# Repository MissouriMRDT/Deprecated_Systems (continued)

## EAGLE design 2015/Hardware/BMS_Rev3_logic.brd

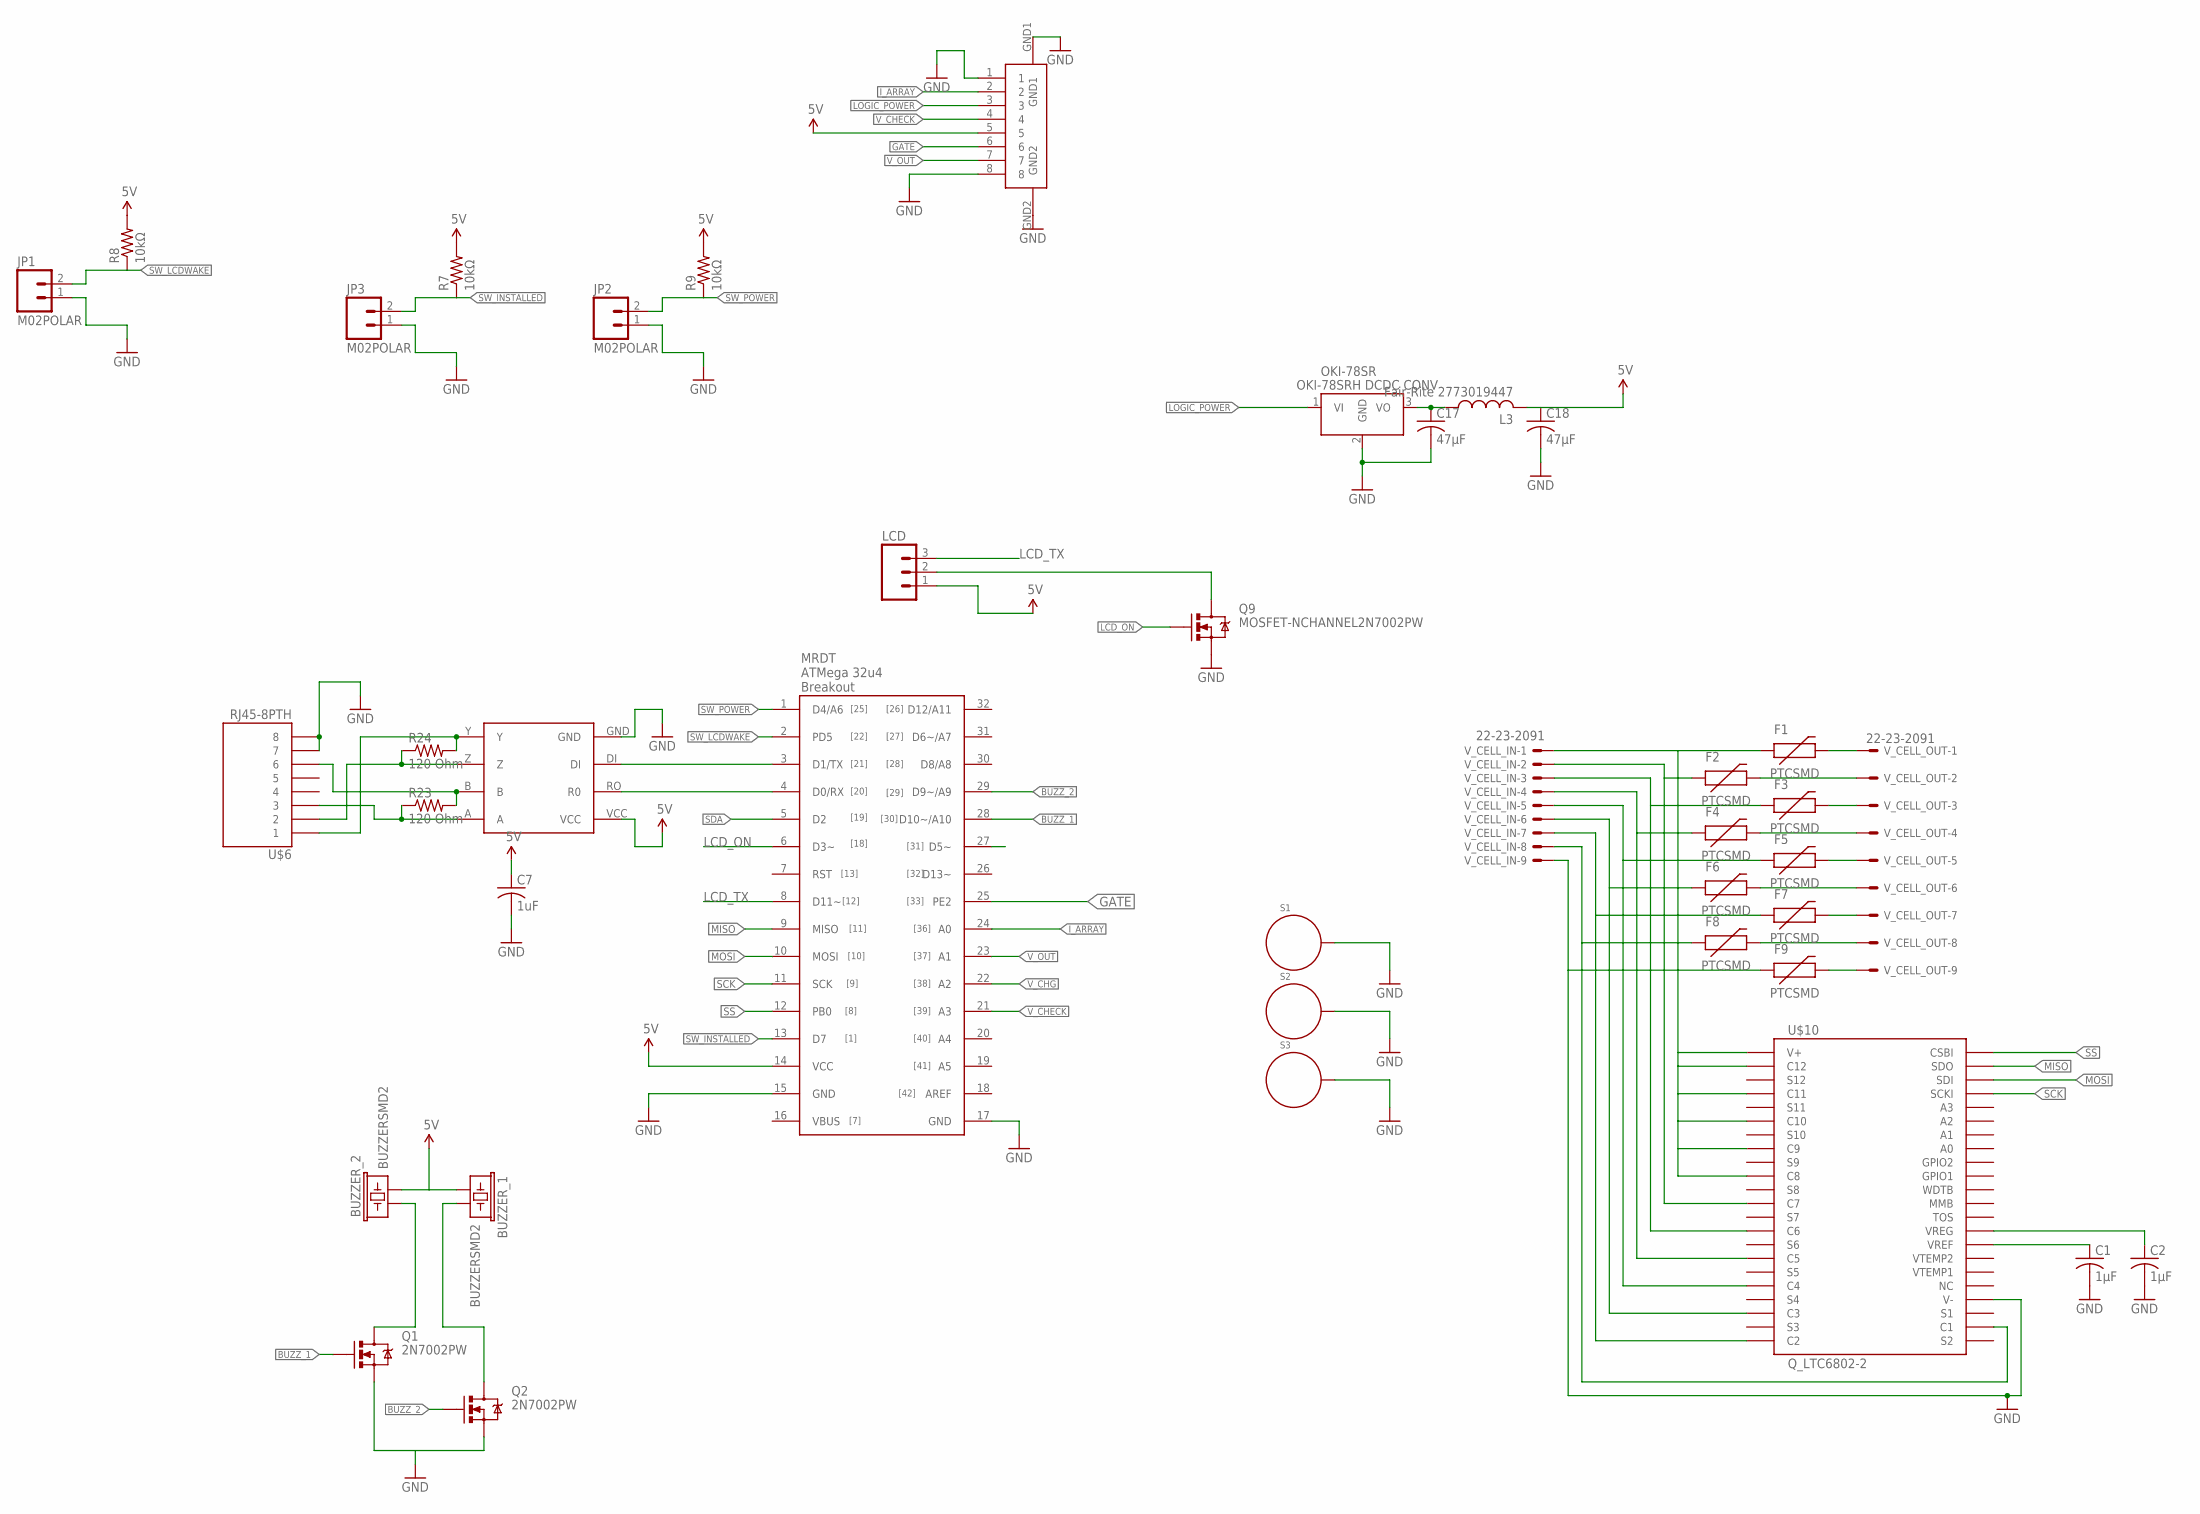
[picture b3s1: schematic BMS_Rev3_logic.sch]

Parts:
BUZZER_1, BUZZER_2: BUZZERSMD2; BUZZER-CCV
C1, C2: 1µF; C1206
C7: 1uF; C1206
C17, C18: 47µF; C1206
F1, F2, F3, F4, F5, F6, F7, F8, F9: PTCSMD; PTC-1206
JP1, JP2, JP3: M02POLAR; MOLEX-1X2
L3: Fair-Rite 2773019447; L4532M
LCD: M03POLAR; MOLEX-1X3
OKI-78SR: Q_OKI-78SR; OKI-78SRH
Q1, Q2: 2N7002PW; SOT323
Q9: MOSFET-NCHANNEL2N7002PW; SOT323
R7, R8, R9: 10kΩ; R1206
R23, R24: 120 Ohm; 1206
S1, S2, S3: STANDOFF_ELECTRICAL; STANDOFF-ELECTRICAL
U$1: 8POS_LOGIC; LOGIC_CONNECT
U$3: 32U4_BREAKOUT; 32U4_MCU_DIP
U$6: RJ45-8PTH; RJ45-8
U$9: MAX3077; MAX3070E
U$10: Q_LTC6802-2; SSOP44
V_CELL_IN: 22-23-2091
V_CELL_OUT: 22-23-2091

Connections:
5V: BUZZER_1.+ (1), BUZZER_2.- (2), C7.1, C18.1, L3.2, LCD.1, R7.2, R8.2, R9.2, U$1.5, U$3.14 (VCC), U$9.VCC
BUZZ_1: Q1.1 (G), U$3.28 (D10~/A10)
BUZZ_2: Q2.1 (G), U$3.29 (D9~/A9)
GATE: U$1.6, U$3.25 (PE2)
GND: C1.2, C2.2, C7.2, C17.2, C18.2, F9.1, JP1.1, JP2.1, JP3.1, OKI-78SR.2 (GND), Q1.2 (S), Q2.2 (S), Q9.2 (S), S1.P1, S2.P1, S3.P1, U$1.1, U$1.8, U$1.GND1, U$1.GND2, U$3.15 (GND), U$3.17 (GND), U$6.7, U$6.8, U$9.GND, U$10.26 (V-), V_CELL_IN.9
I_ARRAY: U$1.2, U$3.24 (A0)
LCD_DB4: U$3.27 (D5~)
LCD_ON: Q9.1 (G), U$3.6 (D3~)
LCD_TX: LCD.3, U$3.8 (D11~)
LOGIC_POWER: OKI-78SR.1 (VI), U$1.3
MISO: U$3.9 (MISO), U$10.43 (SDO)
MOSI: U$3.10 (MOSI), U$10.42 (SDI)
unnamed: F1.2, V_CELL_OUT.1
unnamed: F2.2, V_CELL_OUT.2
unnamed: F3.2, V_CELL_OUT.3
unnamed: F9.2, V_CELL_OUT.9
unnamed: LCD.2, Q9.3 (D)
unnamed: R24.2, U$6.1, U$9.Y
unnamed: R24.1, U$6.2, U$9.Z
unnamed: BUZZER_1.- (2), Q2.3 (D)
unnamed: R23.2, U$6.6, U$9.B
unnamed: R23.1, U$6.3, U$9.A
unnamed: U$3.3 (D1/TX), U$9.DI
unnamed: C1.1, U$10.30 (VREF)
unnamed: C2.1, U$10.31 (VREG)
unnamed: F4.2, V_CELL_OUT.4
unnamed: F5.2, V_CELL_OUT.5
unnamed: F6.2, V_CELL_OUT.6
unnamed: F7.2, V_CELL_OUT.7
unnamed: F8.2, V_CELL_OUT.8
unnamed: BUZZER_2.+ (1), Q1.3 (D)
unnamed: F1.1, U$10.1 (V+), U$10.2 (C12), U$10.4 (C11), U$10.6 (C10), U$10.8 (C9), U$10.10 (C8), V_CELL_IN.1
unnamed: F2.1, U$10.12 (C7), V_CELL_IN.2
unnamed: F3.1, U$10.14 (C6), V_CELL_IN.3
unnamed: F6.1, U$10.20 (C3), V_CELL_IN.6
unnamed: F7.1, U$10.22 (C2), V_CELL_IN.7
unnamed: F8.1, U$10.24 (C1), V_CELL_IN.8
unnamed: F4.1, U$10.16 (C5), V_CELL_IN.4
unnamed: F5.1, U$10.18 (C4), V_CELL_IN.5
unnamed: C17.1, L3.1, OKI-78SR.3 (VO)
RXD: U$3.4 (D0/RX), U$9.RO (R0)
SCK: U$3.11 (SCK), U$10.41 (SCKI)
SDA: U$3.5 (D2)
SS: U$3.12 (PB0), U$10.44 (CSBI)
SW_INSTALLED: JP3.2, R7.1, U$3.13 (D7)
SW_LCDWAKE: JP1.2, R8.1, U$3.2 (PD5)
SW_POWER: JP2.2, R9.1, U$3.1 (D4/A6)
V_CHECK: U$1.4, U$3.21 (A3)
V_CHG: U$3.22 (A2)
V_OUT: U$1.7, U$3.23 (A1)

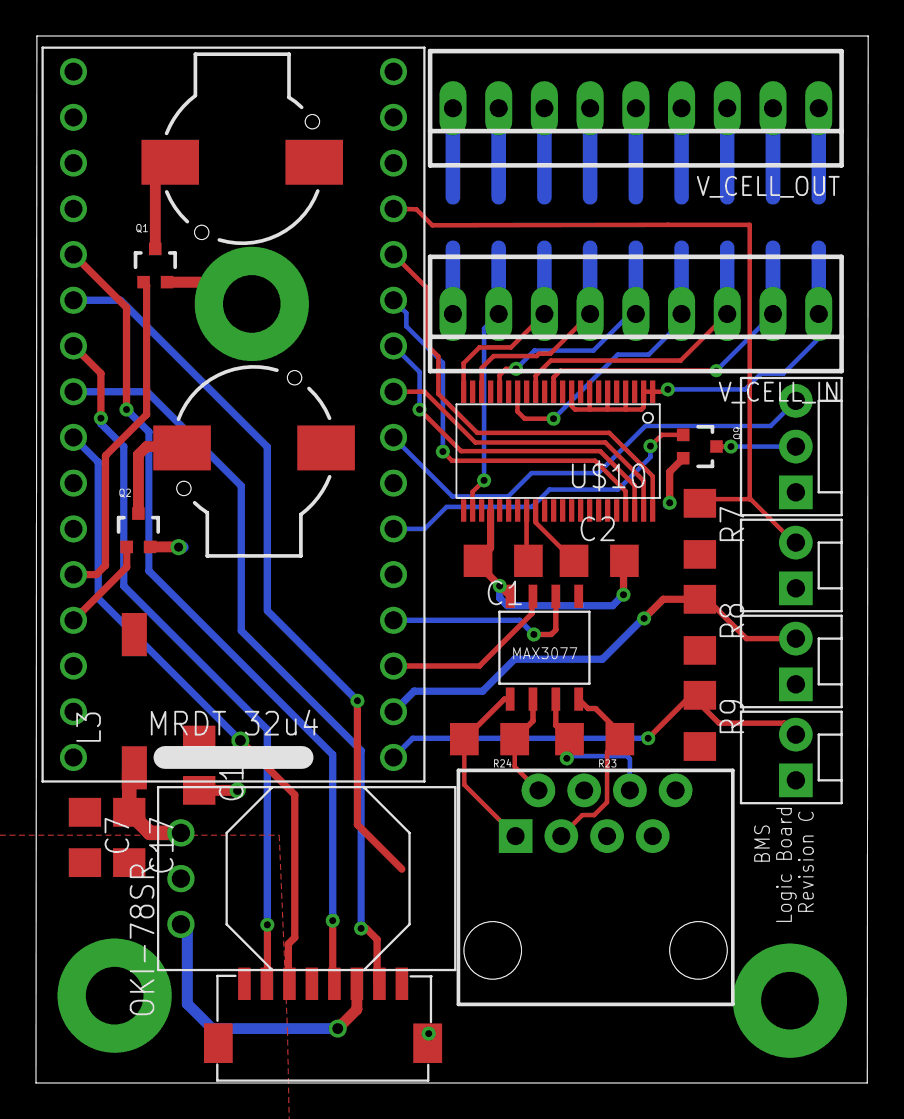
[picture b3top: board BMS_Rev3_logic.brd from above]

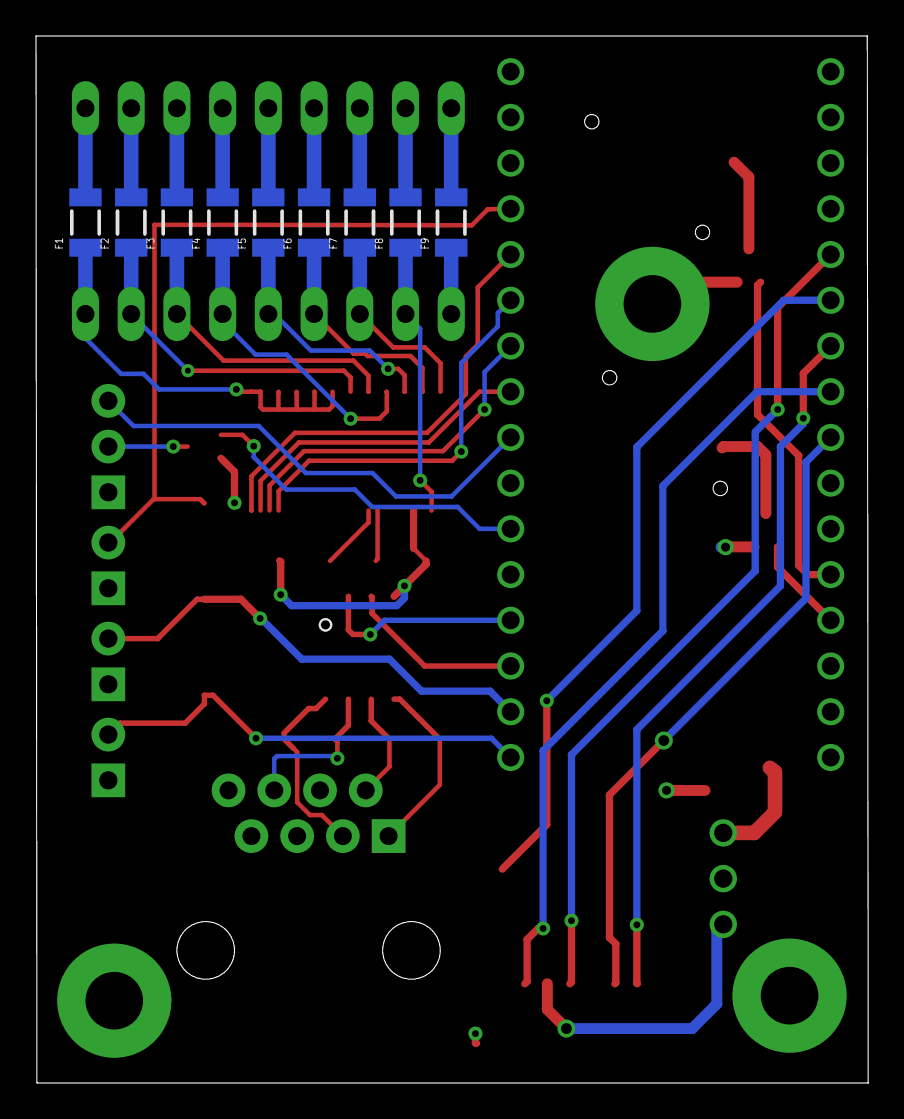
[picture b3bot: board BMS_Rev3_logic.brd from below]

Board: 2 copper layers, 46.2 x 58.2 mm, 40 parts (9 on the bottom side), 47 nets.

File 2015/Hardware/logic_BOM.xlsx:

Quantity | Value | Device | Package | DigiKey ID
1 |  | L-USL3216C
1 |  | M03POLAR
1 |  | M08BM08B-SRSS-TB
1 | 32U4_BREAKOUT | 32U4_BREAKOUT
1 | MAX3077 | MAX3077 |  | MAX3077EESA+-ND
1 | MOSFET-NCHANNEL2N7002PW | MOSFET-NCHANNEL2N7002PW |  | 568-5987-1-ND
1 | Q_LTC6802-2 | Q_LTC6802-2 |  | LTC6802IG-2#PBF-ND
1 | Q_OKI-78SR | Q_OKI-78SR |  | 811-2692-ND
1 | RJ45-8PTH | RJ45-8PTH
2 | 120 Ohm | RESISTOR1206 |  | P120ECT-ND
3 | 1uF | C-USC1206
2 | 22-23-2091 | 22-23-2091 |  | WM4207-ND
2 | 47uF | C-USC1206
2 |  | BUZZERSMD2 |  | 102-1265-1-ND
3 | 10k | R-US_R1206
3 |  | M02POLAR
3 |  | STANDOFF_ELECTRICAL
9 |  | PTCSMD

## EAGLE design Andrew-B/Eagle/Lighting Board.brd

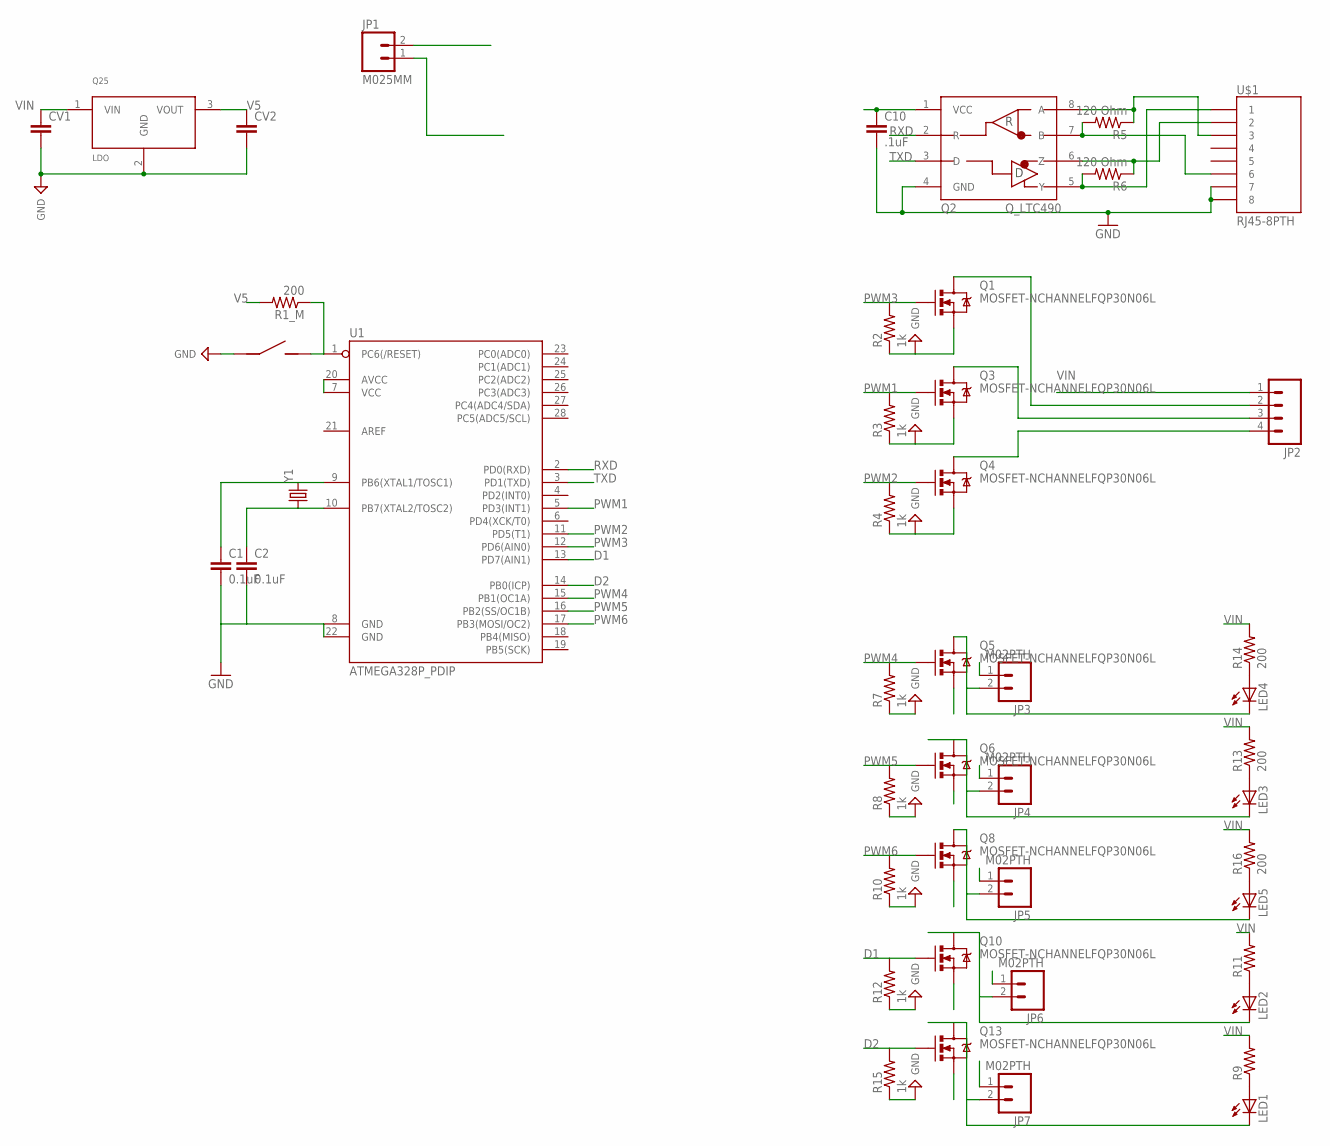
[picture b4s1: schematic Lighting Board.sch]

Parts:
C1, C2: 0.1uF; 1206
C10: .1uF; 1206
CV1, CV2: C_CAP_0805; C_0805
JP1: M025MM; SCREWTERMINAL-5MM-2
JP2: M04PTH; 1X04
JP3, JP4, JP5, JP6, JP7: M02PTH; 1X02
LED1, LED2, LED3, LED4, LED5: LED1206; LED-1206
MS: J_MC32857; J_TOGGLE
Q1, Q3, Q4, Q5, Q6, Q8, Q10, Q13: MOSFET-NCHANNELFQP30N06L; TO220V
Q2: Q_LTC490; DIP8
Q25: LDO; TO-220
R1_M: 200; R_0805
R2, R3, R4, R7, R8, R10, R12, R15: 1k; 1206
R5, R6: 120 Ohm; 1206
R9, R11: RESISTOR1206; 1206
R13, R14, R16: 200; 1206
U1: ATMEGA328P_PDIP; DIL28-3
U$1: RJ45-8PTH; RJ45-8
Y1: CRYSTALHC49US; HC49US

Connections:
D1: Q10.1 (G), R12.2, U1.13 (PD7(AIN1))
D2: Q13.1 (G), R15.2, U1.14 (PB0(ICP))
GND: C1.2, C2.2, C10.2, CV1.2, CV2.2, JP1.2, MS.P$1 (1), Q1.3 (S), Q2.4 (GND), Q3.3 (S), Q4.3 (S), Q5.3 (S), Q6.3 (S), Q8.3 (S), Q10.3 (S), Q13.3 (S), Q25.2 (GND), R2.1, R3.1, R4.1, R7.1, R8.1, R10.1, R12.1, R15.1, U1.8 (GND), U1.22 (GND), U$1.7, U$1.8
unnamed: Q2.5 (Y), R6.2, U$1.1
unnamed: C2.1, U1.10 (PB7(XTAL2/TOSC2)), Y1.1
unnamed: LED1.A, R9.1
unnamed: LED2.A, R11.1
unnamed: LED3.A, R13.1
unnamed: LED4.A, R14.1
unnamed: LED5.A, R16.1
unnamed: Q2.6 (Z), R6.1, U$1.2
unnamed: Q2.7 (B), R5.2, U$1.6
unnamed: Q2.8 (A), R5.1, U$1.3
unnamed: C1.1, U1.9 (PB6(XTAL1/TOSC1)), Y1.2
unnamed: JP2.2, Q1.2 (D)
unnamed: JP2.3, Q3.2 (D)
unnamed: JP2.4, Q4.2 (D)
unnamed: MS.P$2 (2), R1_M.1, U1.1 (PC6(/RESET))
N%2: JP4.2, LED3.C, Q6.2 (D)
N%3: JP3.2, LED4.C, Q5.2 (D)
N%106: JP5.2, LED5.C, Q8.2 (D)
N%107: JP6.2, LED2.C, Q10.2 (D)
N%110: JP7.2, LED1.C, Q13.2 (D)
PWM1: Q3.1 (G), R3.2, U1.5 (PD3(INT1))
PWM2: Q4.1 (G), R4.2, U1.11 (PD5(T1))
PWM3: Q1.1 (G), R2.2, U1.12 (PD6(AIN0))
PWM4: Q5.1 (G), R7.2, U1.15 (PB1(OC1A))
PWM5: Q6.1 (G), R8.2, U1.16 (PB2(SS/OC1B))
PWM6: Q8.1 (G), R10.2, U1.17 (PB3(MOSI/OC2))
RXD: Q2.2 (R), U1.2 (PD0(RXD))
TXD: Q2.3 (D), U1.3 (PD1(TXD))
V5: C10.1, CV2.1, Q2.1 (VCC), Q25.3 (VOUT), R1_M.2, U1.7 (VCC), U1.20 (AVCC)
VIN: CV1.1, JP1.1, JP2.1, JP3.1, JP4.1, JP5.1, JP6.1, JP7.1, Q25.1 (VIN), R9.2, R11.2, R13.2, R14.2, R16.2

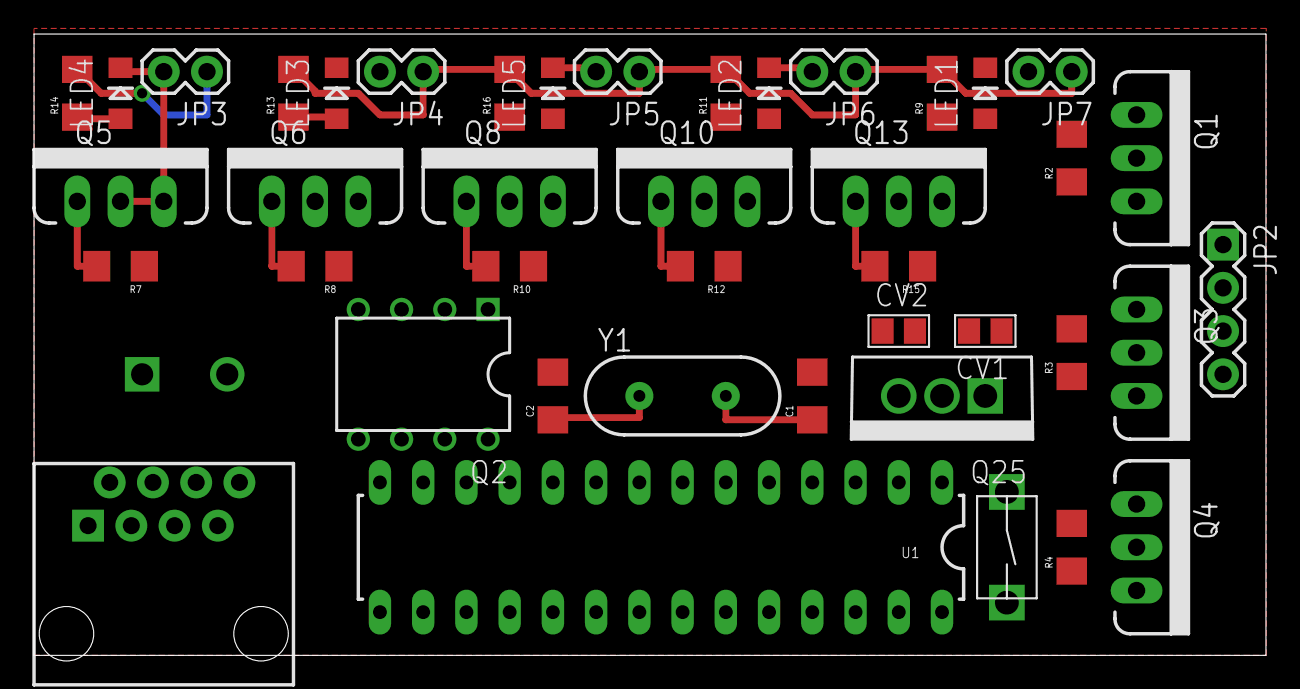
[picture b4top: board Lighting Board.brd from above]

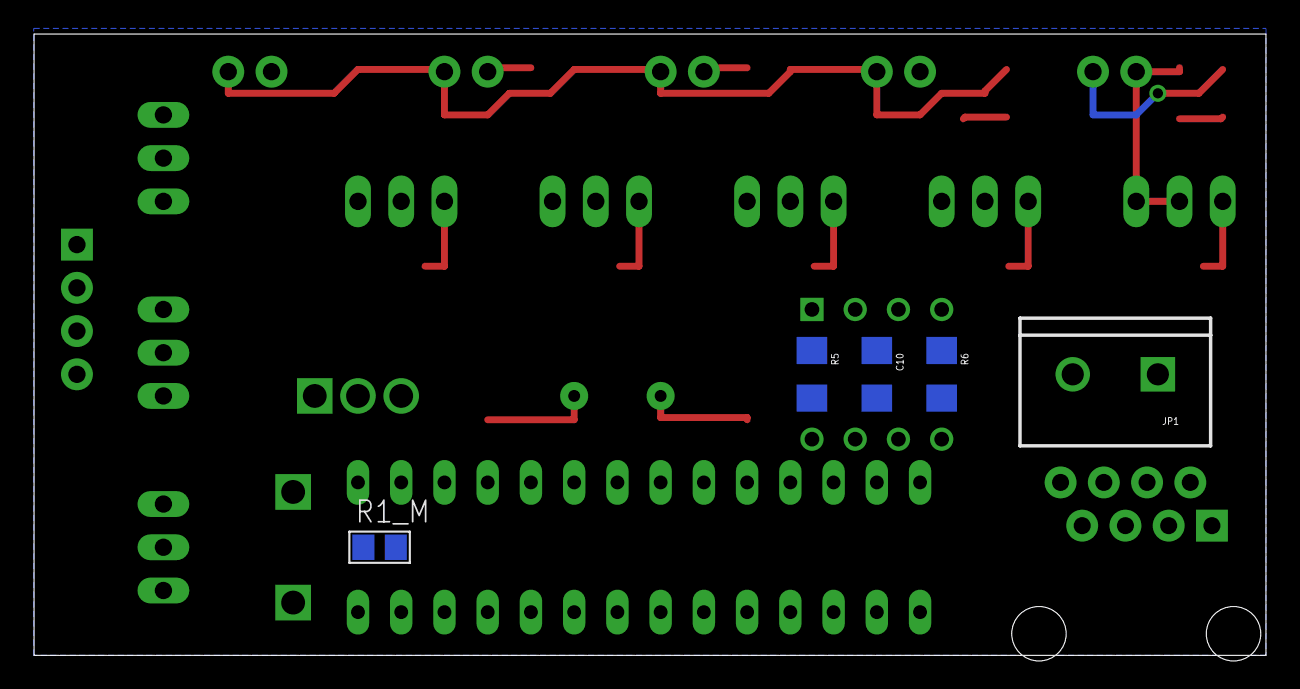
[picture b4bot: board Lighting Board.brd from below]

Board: 2 copper layers, 72.4 x 36.5 mm, 47 parts (5 on the bottom side), 33 nets.
